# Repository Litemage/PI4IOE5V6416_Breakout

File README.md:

# Repo Description
This project contains a breakout board for the Diodes Inc. PI4IOE5V6416 16 channel I2C I/O expander, as well as a C driver, for easier incorporation into your projects.

[The datasheet can be found here](https://www.diodes.com/assets/Datasheets/PI4IOE5V6416.pdf).

# Hardware
The ECad tool of choice is KiCad for this project. 

Manufacturing files for revision 3.0 are available in the **/Manufacturing** directory.

Photos of the board are available in **/photos**

The schematic is available in the root directory as a pdf. 

# Driver \(C\)
The C driver is designed to be implementation-agnostic. I recommend reading through the header files to gain a better understanding of the driver itself, and what's available. Regardless, the driver works off of a handle principle:

You create a device handle that is populated with call-backs to all the different functions needed to communicate with the device (read / write). 

This handle is then passed to all the functions in the public API which read/write to the device.

There is currently one driver implementation example under **/Examples**. Open an issue for another example if the simple one isn't enough as a quick-start to the driver.

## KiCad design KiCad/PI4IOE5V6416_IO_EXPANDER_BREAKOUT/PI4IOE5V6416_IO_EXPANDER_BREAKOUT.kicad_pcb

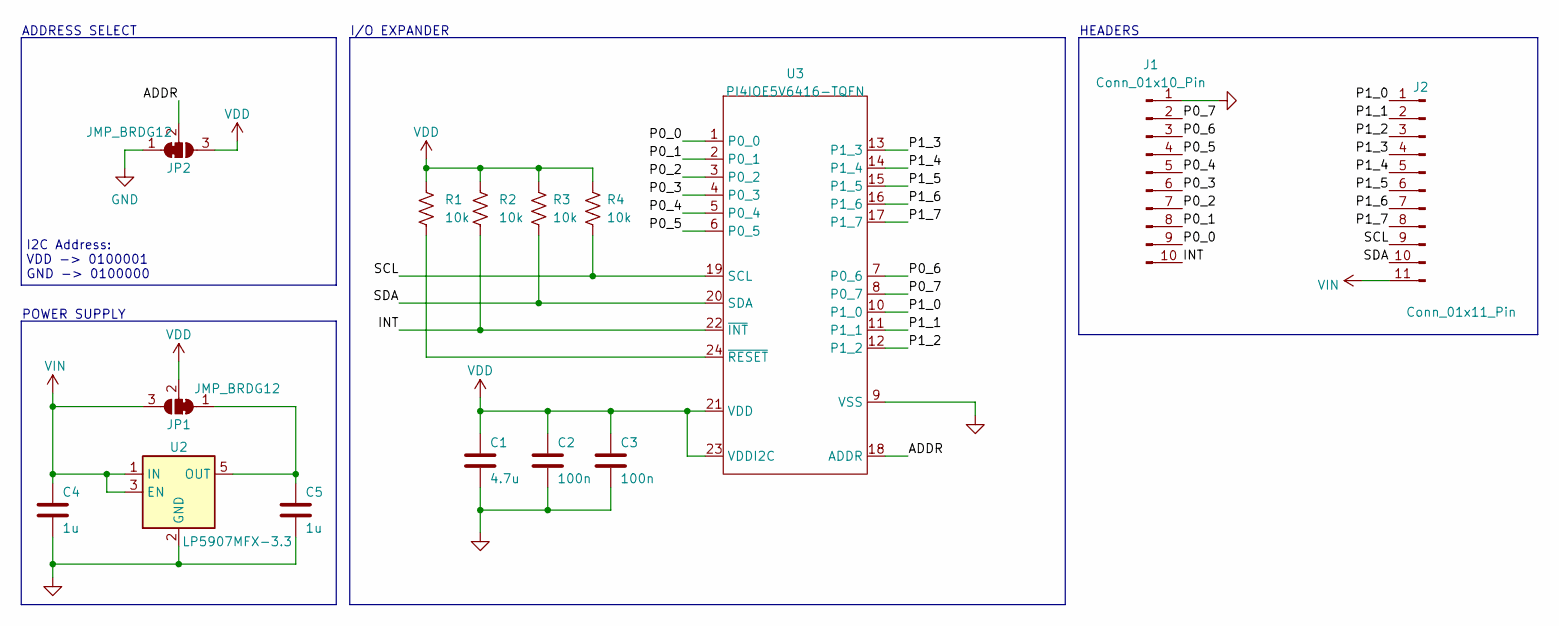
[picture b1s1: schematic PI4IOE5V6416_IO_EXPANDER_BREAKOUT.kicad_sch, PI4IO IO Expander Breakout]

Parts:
C1: 4.7u; C_0603_1608Metric
C2, C3: 100n; C_0603_1608Metric
C4, C5: 1u; C_0603_1608Metric
J1: Conn_01x10_Pin; PinHeader_1x10_P2.54mm_Vertical
J2: Conn_01x11_Pin; PinHeader_1x11_P2.54mm_Vertical
JP1, JP2: JMP_BRDG12; SolderJumper-3_P1.3mm_Bridged12_RoundedPad1.0x1.5mm
R1, R2, R3, R4: 10k; R_0603_1608Metric
U2: LP5907MFX-3.3; SOT-23-5
U3: PI4IOE5V6416-TQFN; TQFN-24-1EP_4x4mm_P0.5mm_EP2.1x2.1mm

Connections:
/ADDR: JP2.2 (C), U3.18 (ADDR)
/INT: J1.10, R2.2, U3.22 (~INT)
/P0_0: J1.9, U3.1 (P0_0)
/P0_1: J1.8, U3.2 (P0_1)
/P0_2: J1.7, U3.3 (P0_2)
/P0_3: J1.6, U3.4 (P0_3)
/P0_4: J1.5, U3.5 (P0_4)
/P0_5: J1.4, U3.6 (P0_5)
/P0_6: J1.3, U3.7 (P0_6)
/P0_7: J1.2, U3.8 (P0_7)
/P1_0: J2.1, U3.10 (P1_0)
/P1_1: J2.2, U3.11 (P1_1)
/P1_2: J2.3, U3.12 (P1_2)
/P1_3: J2.4, U3.13 (P1_3)
/P1_4: J2.5, U3.14 (P1_4)
/P1_5: J2.6, U3.15 (P1_5)
/P1_6: J2.7, U3.16 (P1_6)
/P1_7: J2.8, U3.17 (P1_7)
/SCL: J2.9, R4.2, U3.19 (SCL)
/SDA: J2.10, R3.2, U3.20 (SDA)
GND: C1.2, C2.2, C3.2, C4.2, C5.2, J1.1, JP2.1 (A), U2.2 (GND), U3.9 (VSS)
unnamed: C5.1, JP1.1 (A), U2.5 (OUT)
unnamed: R1.2, U3.24 (~RESET)
VDD: C1.1, C2.1, C3.1, JP1.2 (C), JP2.3 (B), R1.1, R2.1, R3.1, R4.1, U3.21 (VDD), U3.23 (VDDI2C)
VIN: C4.1, J2.11, JP1.3 (B), U2.1 (IN), U2.3 (EN)

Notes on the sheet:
POWER SUPPLY
ADDRESS SELECT
HEADERS
I2C Address: VDD -> 0100001 GND -> 0100000
I/O EXPANDER

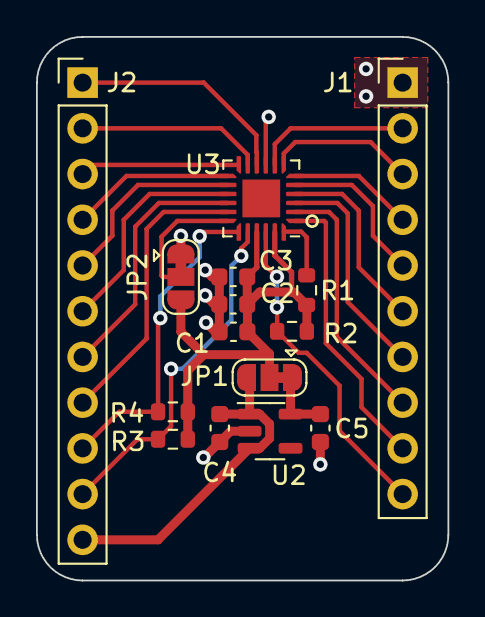
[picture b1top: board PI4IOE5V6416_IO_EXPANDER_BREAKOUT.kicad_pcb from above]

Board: 2 copper layers, 22.9 x 30.2 mm, 15 parts (0 on the bottom side), 25 nets.

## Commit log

2023-09-06 Add License
2023-09-06 Revision 4
    - Remove unnecessary pin headers
2023-09-07 Add driver example
2023-10-07 Fix Schematic
2024-11-19 Resolve potential bugs
    - FIX: Delay mircoseconds declared with 8-bit buffer
    - FIX: Potential infinitely recursive call (oops)
2024-11-27 Pass address to port functions
